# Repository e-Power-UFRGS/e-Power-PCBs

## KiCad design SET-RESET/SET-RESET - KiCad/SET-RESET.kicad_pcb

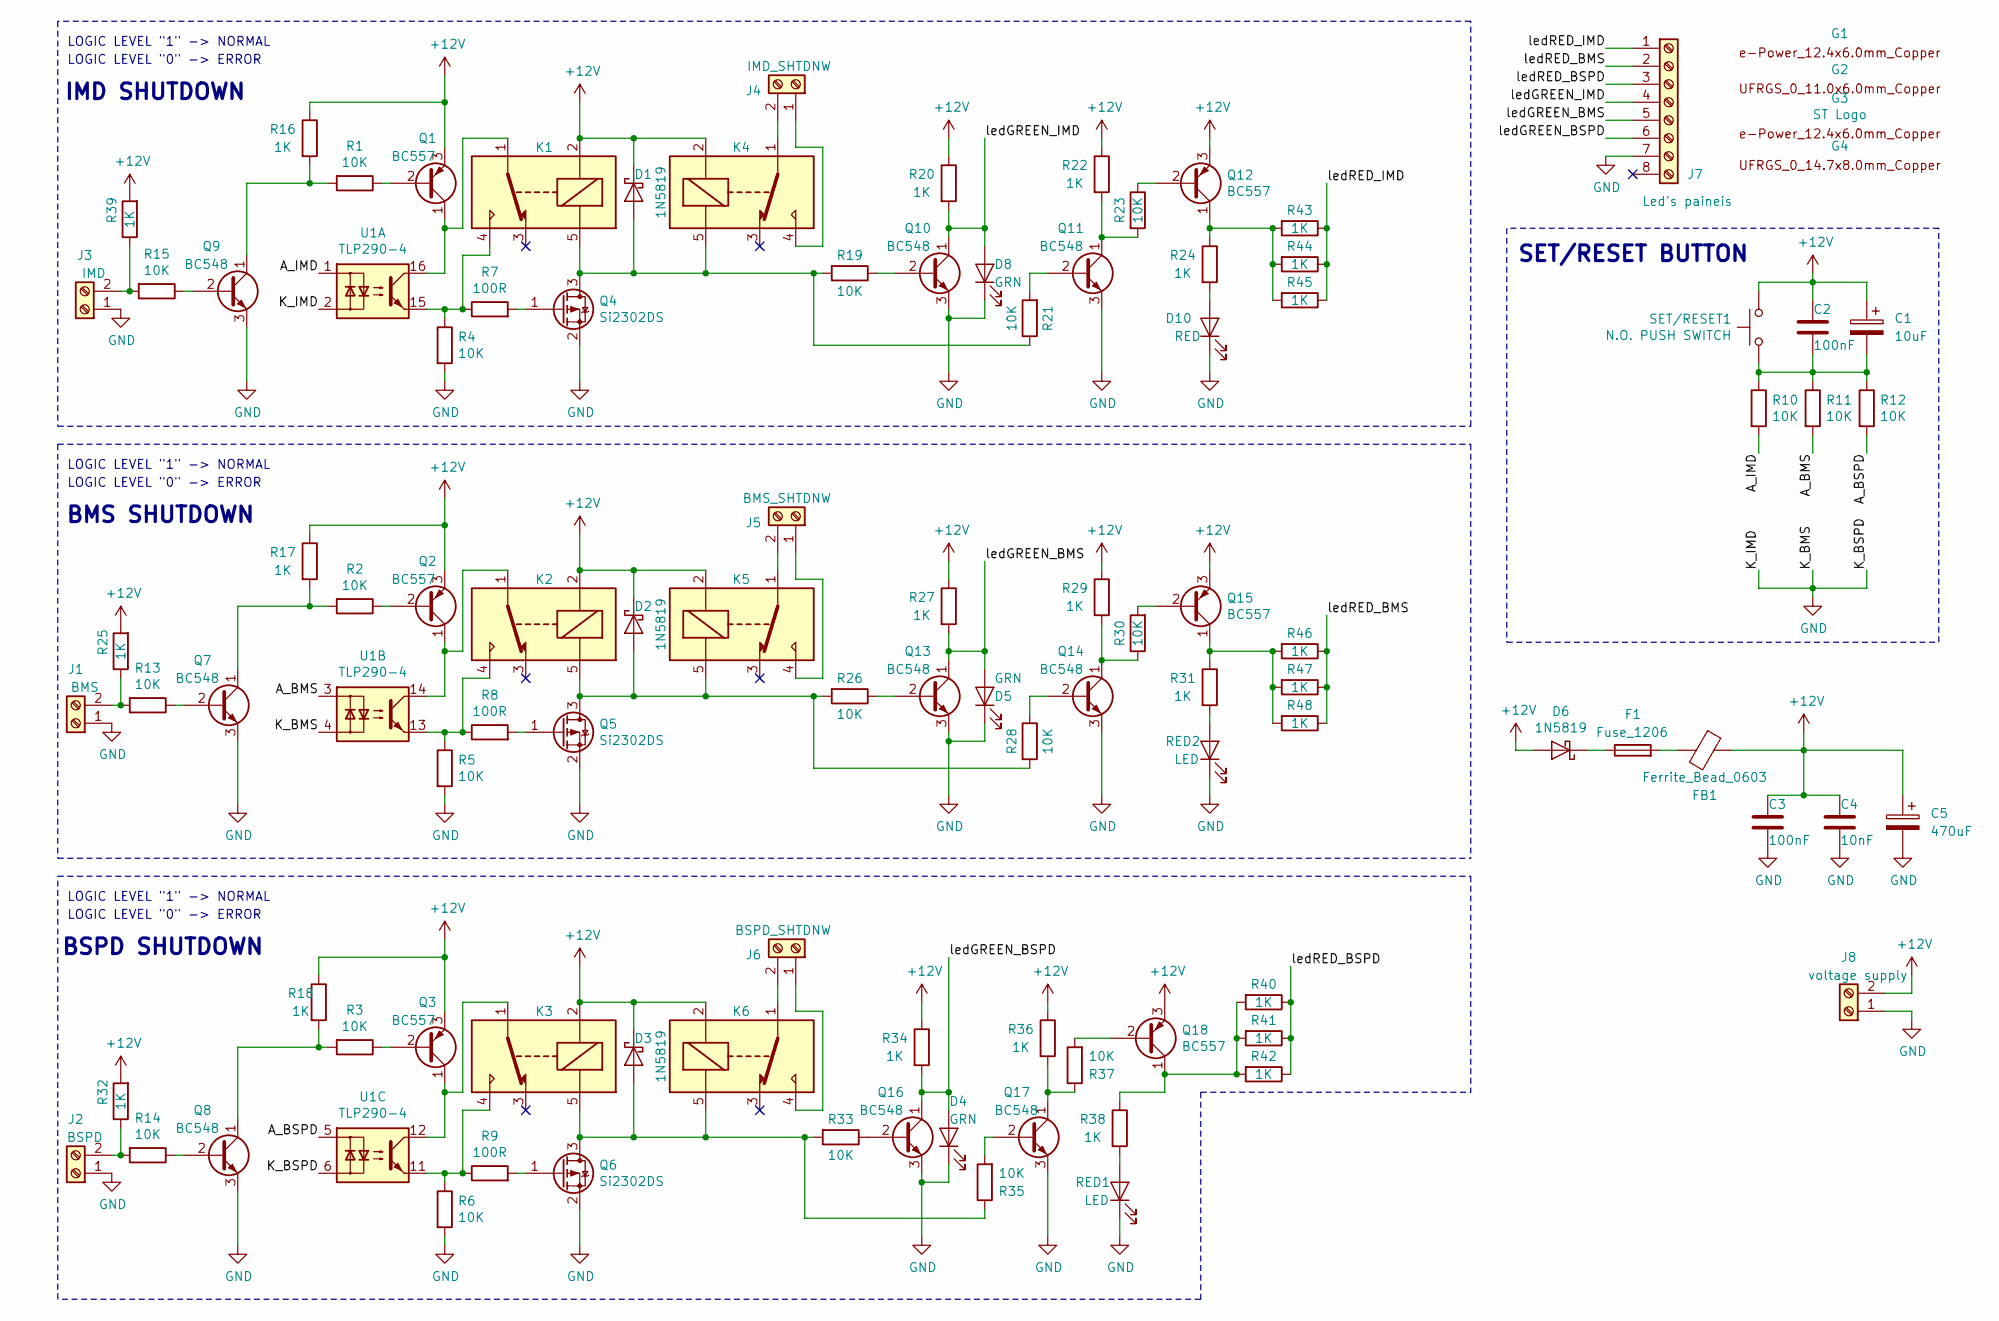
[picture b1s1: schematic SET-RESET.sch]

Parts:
C1: 10uF; CP_Elec_4x5.3
C2, C3: 100nF; C_0603_1608Metric_Pad1.05x0.95mm_HandSolder
C4: 10nF; C_0603_1608Metric_Pad1.05x0.95mm_HandSolder
C5: 470uF; CP_Elec_4x5.3
D1, D2, D3, D6: 1N5819; DO-41_SMD
D4, D5, D8: GRN; LED_0805_1.15x1.40mm_HandSolder
D10: RED; LED_0805_1.15x1.40mm_HandSolder
F1: Fuse_1206; FUSE_1206_3216Metric
FB1: Ferrite_Bead_0603; FB_0603_1608Metric
G1: e-Power_12.4x6.0mm_Copper; e-Power_16.5x8.0mm_Copper
G2: UFRGS_1_11.0x6.0mm_Copper; ESD-Logo_8.9x8mm_Copper
G3: ST Logo; ST_6.5x4.1mm_Copper
G4: UFRGS_1_14.7x8.0mm_Copper; UFRGS_14.7x8.0mm_Copper
J1: BMS; PhoenixContact_GMSTBA_2,5_2-G_1x02_P7.50mm_Horizontal
J2: BSPD; PhoenixContact_GMSTBA_2,5_2-G_1x02_P7.50mm_Horizontal
J3: IMD; PhoenixContact_GMSTBA_2,5_2-G_1x02_P7.50mm_Horizontal
J4: IMD_SHTDNW; PhoenixContact_GMSTBA_2,5_2-G_1x02_P7.50mm_Horizontal
J5: BMS_SHTDNW; PhoenixContact_GMSTBA_2,5_2-G_1x02_P7.50mm_Horizontal
J6: BSPD_SHTDNW; PhoenixContact_GMSTBA_2,5_2-G_1x02_P7.50mm_Horizontal
J7: Led's paineis; PinHeader_1x08_P1.27mm_Vertical
J8: voltage supply; PhoenixContact_GMSTBA_2,5_2-G_1x02_P7.50mm_Horizontal
K1, K2, K3, K4, K5, K6: RELAY_19.1x15.5mm; Relay_SPDT_SANYOU_SRD
Q1, Q2, Q3, Q12, Q15, Q18: BC557; SOT-23
Q4, Q5, Q6: Si2302DS; SOT-23
Q7, Q8, Q9, Q10, Q11, Q13, Q14, Q16, Q17: BC548; SOT-23
R1, R2, R3, R4, R5, R6, R10, R11, R12, R13, R14, R15, R19, R21, R23, R26, R28, R30, R33, R35, R37: 10K; R_1206_3216Metric
R7, R8, R9: 100R; R_1206_3216Metric
R16, R17, R18, R20, R22, R24, R25, R27, R29, R31, R32, R34, R36, R38, R39, R40, R41, R42, R43, R44, R45, R46, R47, R48: 1K; R_1206_3216Metric
RED1, RED2: LED; LED_0805_1.15x1.40mm_HandSolder
SET/RESET1: SW_Push; PhoenixContact_GMSTBA_2,5_2-G_1x02_P7.50mm_Horizontal
U1: TLP290-4

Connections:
+12V: C1.1, C2.1, C3.1, C4.1, C5.1, D1.1 (K), D2.1 (K), D3.1 (K), D6.2 (A), FB1.1, J8.2, K1.2, K2.2, K3.2, K4.2, K5.2, K6.2, Q1.3 (E), Q2.3 (E), Q3.3 (E), Q12.3 (E), Q15.3 (E), Q18.3 (E), R16.1, R17.1, R18.1, R20.1, R22.1, R25.2, R27.1, R29.1, R32.2, R34.1, R36.1, R39.2, SET/RESET1.1
/A_BMS: R11.2, U1.3
/A_BSPD: R12.2, U1.5
/A_IMD: R10.2, U1.1
/ledGREEN_BMS: D5.2 (A), J7.5, Q13.1 (C), R27.2
/ledGREEN_BSPD: D4.2 (A), J7.6, Q16.1 (C), R34.2
/ledGREEN_IMD: D8.2 (A), J7.4, Q10.1 (C), R20.2
/ledRED_BMS: J7.2, R46.1, R47.1, R48.1
/ledRED_BSPD: J7.3, R40.1, R41.1, R42.1
/ledRED_IMD: J7.1, R43.1, R44.1, R45.1
GND: C3.2, C4.2, C5.2, D4.1 (K), D5.1 (K), D8.1 (K), D10.1 (K), J1.1, J2.1, J3.1, J7.7, J8.1, Q4.2 (S), Q5.2 (S), Q6.2 (S), Q7.3 (E), Q8.3 (E), Q9.3 (E), Q10.3 (E), Q11.3 (E), Q13.3 (E), Q14.3 (E), Q16.3 (E), Q17.3 (E), R4.2, R5.2, R6.2, RED1.1 (K), RED2.1 (K), U1.2, U1.4, U1.6
unnamed: C1.2, C2.2, R10.1, R11.1, R12.1, SET/RESET1.2
unnamed: D1.2 (A), K1.5, K4.5, Q4.3 (D), R19.2, R21.1
unnamed: D2.2 (A), K2.5, K5.5, Q5.3 (D), R26.2, R28.2
unnamed: D3.2 (A), K3.5, K6.5, Q6.3 (D), R33.2, R35.1
unnamed: D6.1 (K), F1.1
unnamed: D10.2 (A), R24.2
unnamed: F1.2, FB1.2
unnamed: J1.2, R13.2, R25.1
unnamed: J2.2, R14.2, R32.1
unnamed: J3.2, R15.2, R39.1
unnamed: J4.1, K4.4
unnamed: J4.2, K4.1
unnamed: J5.1, K5.4
unnamed: J5.2, K5.1
unnamed: J6.1, K6.4
unnamed: J6.2, K6.1
unnamed: K1.1, Q1.1 (C), U1.16
unnamed: K1.4, R4.1, R7.1, U1.15
unnamed: K2.1, Q2.1 (C), U1.14
unnamed: K2.4, R5.1, R8.1, U1.13
unnamed: K3.1, Q3.1 (C), U1.12
unnamed: K3.4, R6.1, R9.1, U1.11
unnamed: Q1.2 (B), R1.1
unnamed: Q2.2 (B), R2.1
unnamed: Q3.2 (B), R3.1
unnamed: Q4.1 (G), R7.2
unnamed: Q5.1 (G), R8.2
unnamed: Q6.1 (G), R9.2
unnamed: Q7.1 (C), R2.2, R17.2
unnamed: Q7.2 (B), R13.1
unnamed: Q8.1 (C), R3.2, R18.2
unnamed: Q8.2 (B), R14.1
unnamed: Q9.1 (C), R1.2, R16.2
unnamed: Q9.2 (B), R15.1
unnamed: Q10.2 (B), R19.1
unnamed: Q11.1 (C), R22.2, R23.2
unnamed: Q11.2 (B), R21.2
unnamed: Q12.1 (C), R24.1, R43.2, R44.2, R45.2
unnamed: Q12.2 (B), R23.1
unnamed: Q13.2 (B), R26.1
unnamed: Q14.1 (C), R29.2, R30.1
unnamed: Q14.2 (B), R28.1
unnamed: Q15.1 (C), R31.1, R46.2, R47.2, R48.2
unnamed: Q15.2 (B), R30.2
unnamed: Q16.2 (B), R33.1
unnamed: Q17.1 (C), R36.2, R37.1
unnamed: Q17.2 (B), R35.2
unnamed: Q18.1 (C), R38.1, R40.2, R41.2, R42.2
unnamed: Q18.2 (B), R37.2
unnamed: R31.2, RED2.2 (A)
unnamed: R38.2, RED1.2 (A)

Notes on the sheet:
LOGIC LEVEL "1" -> NORMAL
LOGIC LEVEL "0" -> ERROR
BMS SHUTDOWN
SET/RESET BUTTON
IMD SHUTDOWN
BSPD SHUTDOWN

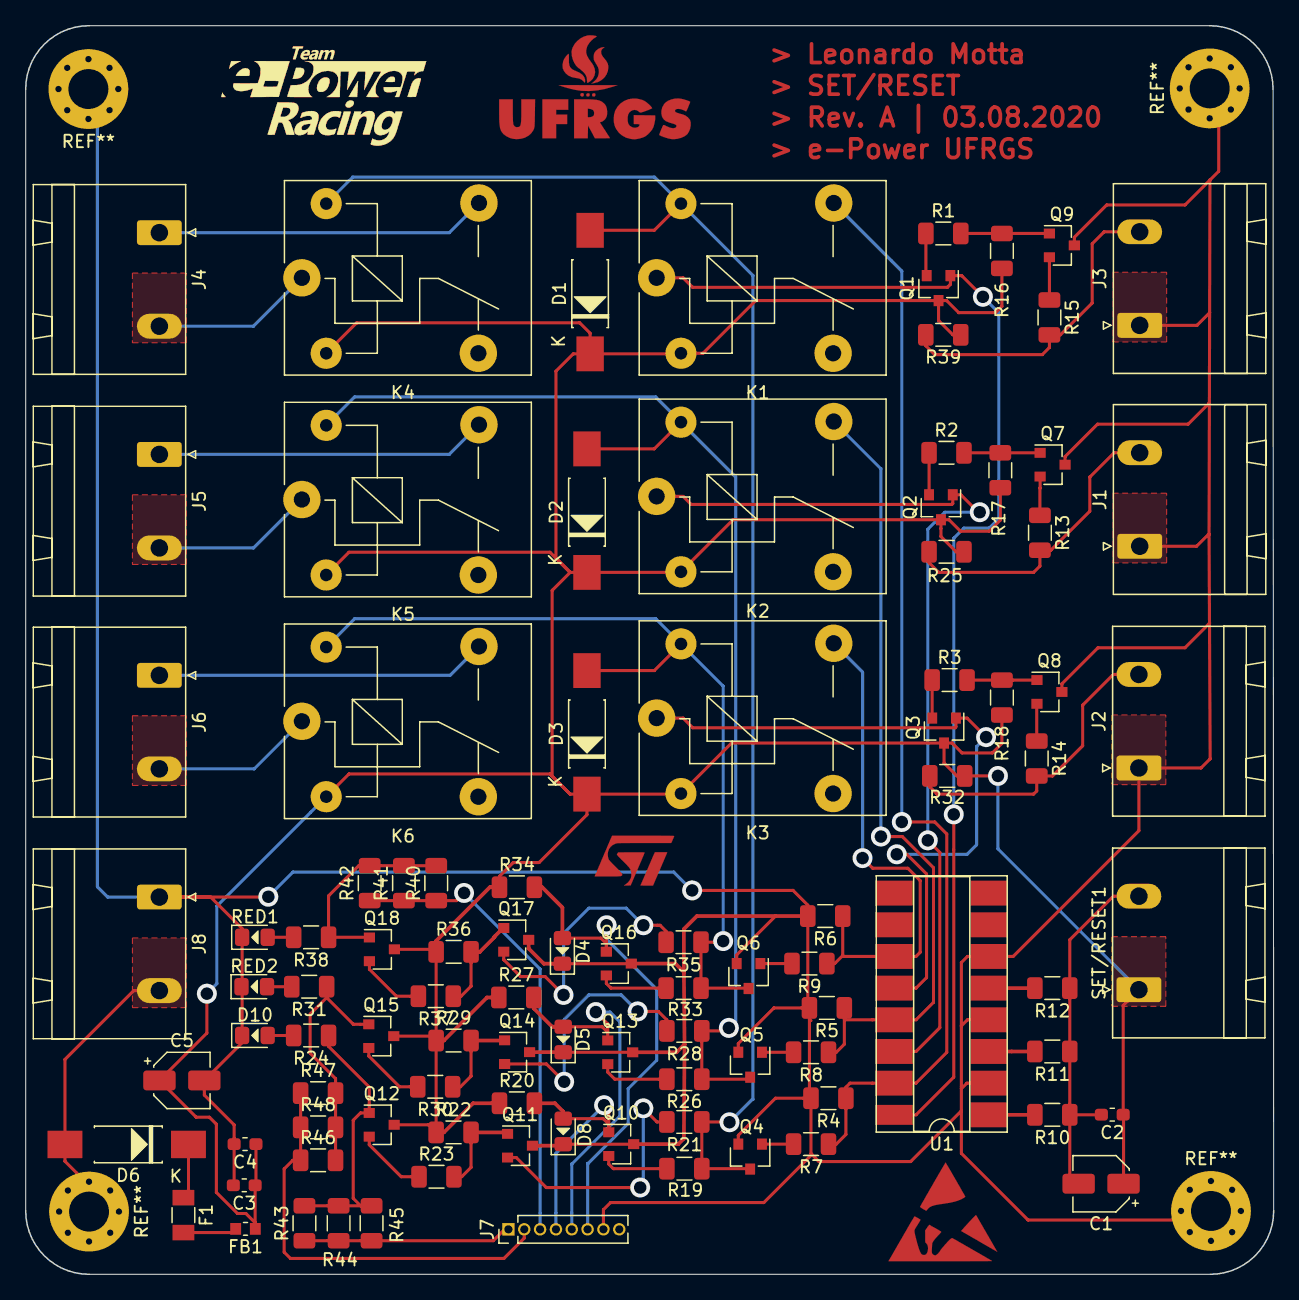
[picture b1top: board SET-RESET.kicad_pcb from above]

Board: 2 copper layers, 100.1 x 100.1 mm, 103 parts (0 on the bottom side), 62 nets.

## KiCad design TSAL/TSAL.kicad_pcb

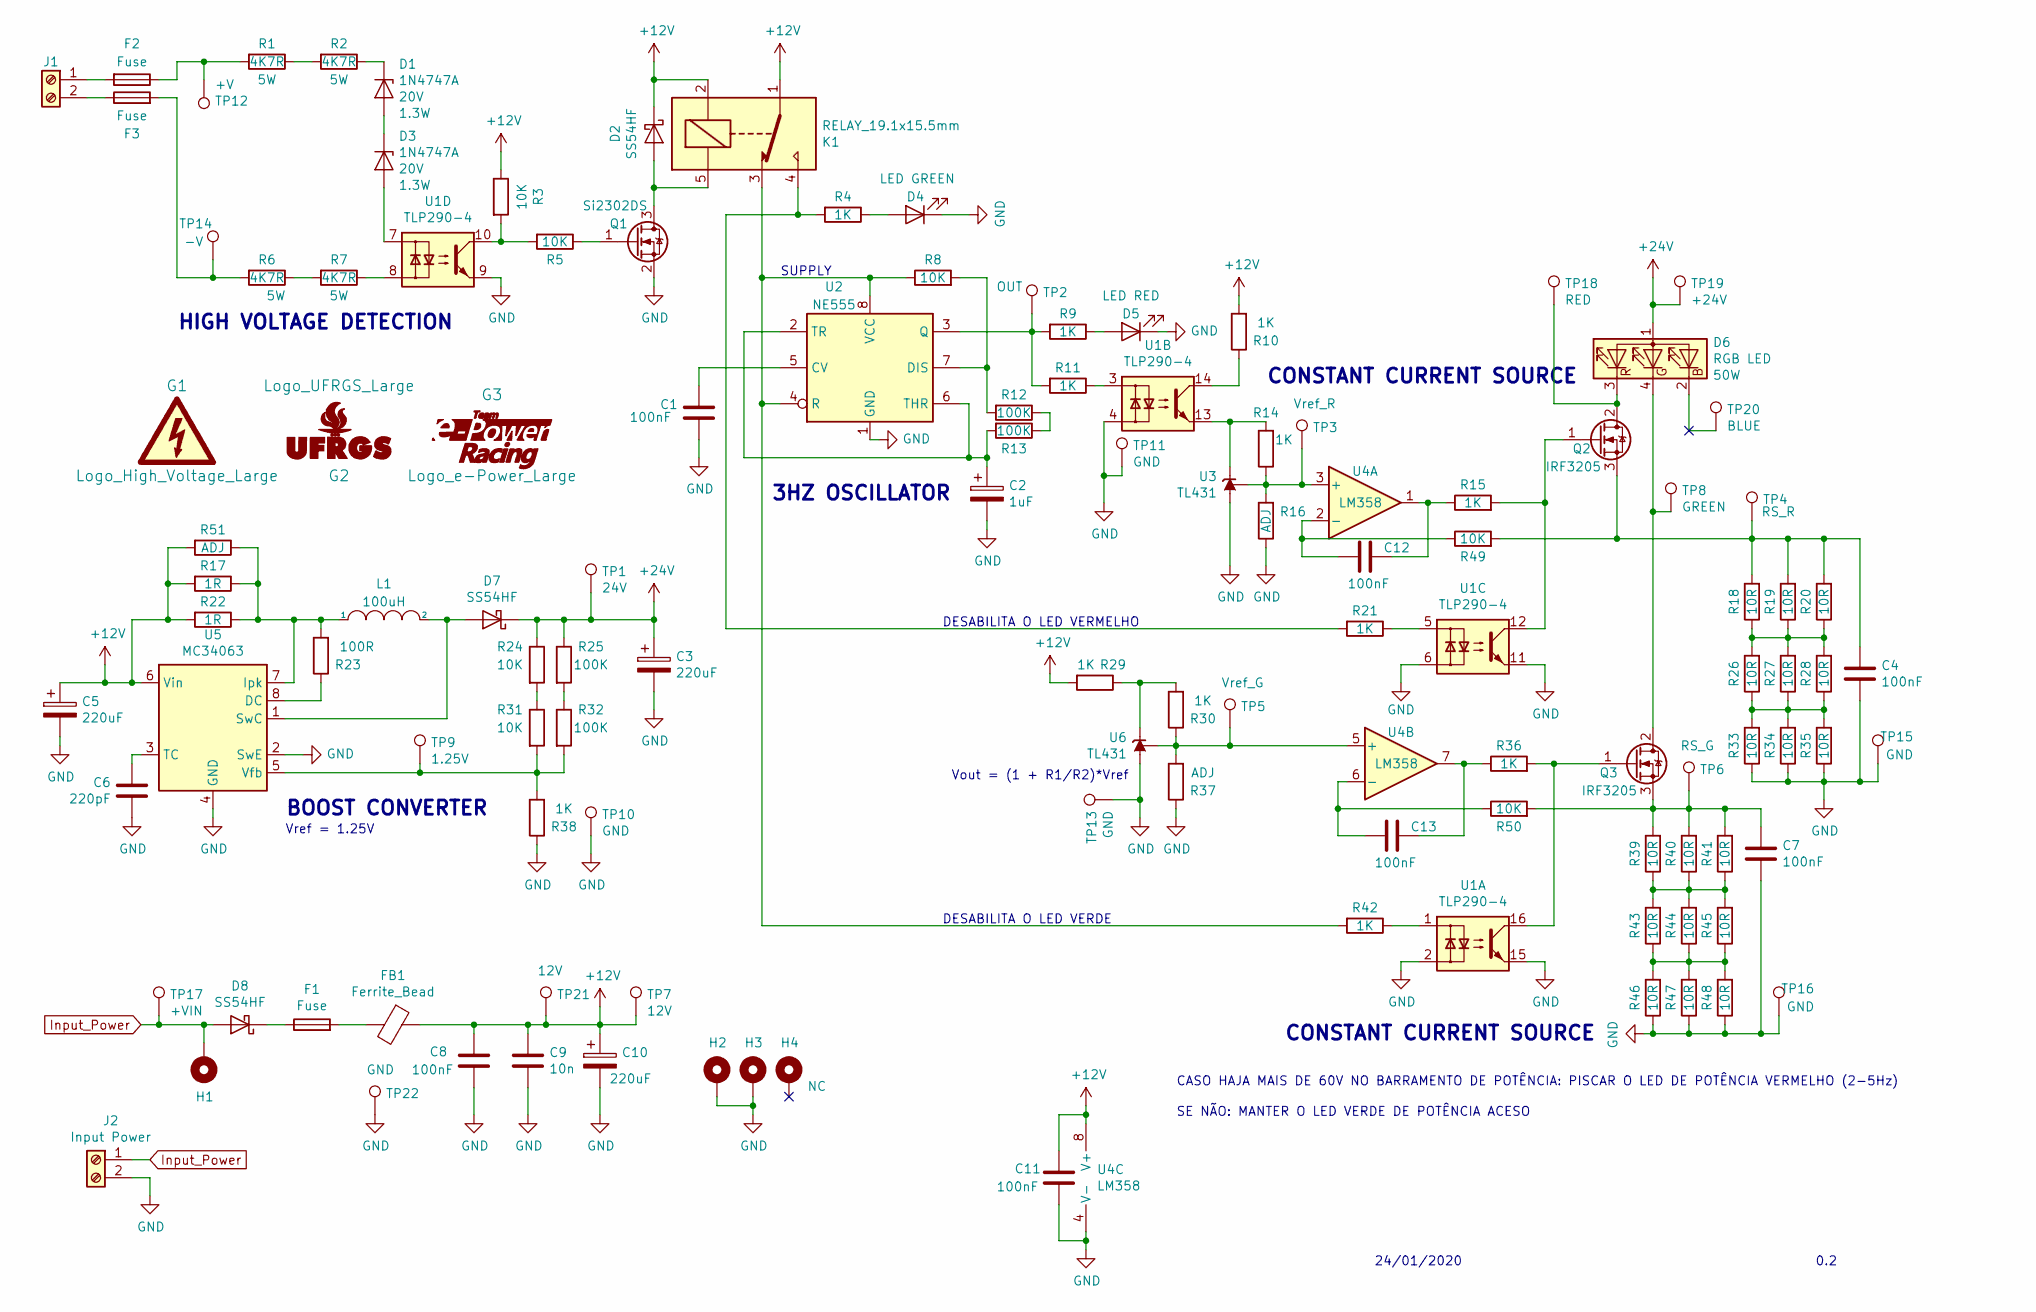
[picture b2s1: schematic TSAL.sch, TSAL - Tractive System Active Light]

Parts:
C1, C4, C7, C8, C11, C12, C13: 100nF; C_0805_2012Metric; Voltage 50V; LCSC C49678
C2: 1uF; C_0805_2012Metric; Voltage 50V; LCSC C28323
C3, C5, C10: 220uF; CP_Elec_10x10; LCSC C311611
C6: 220pF; C_0805_2012Metric; Voltage 50V; LCSC C53172
C9: 10n; C_0805_2012Metric; LCSC C1710
D1, D3: 1N4747A; DO-35_SMD; Voltage 20V
D2, D7, D8: SS54HF; DO-214AC; LCSC C22452
D4: LED GREEN; LED_0603_1608Metric; LCSC C72043
D5: LED RED; LED_0603_1608Metric; LCSC C2286
D6: RGB LED; TerminalBlock_Phoenix_MKDS-1,5-4-5.08_1x04_P5.08mm_Horizont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
F1, F2, F3: Fuse; FUSE_1206_3216Metric; LCSC C182445
FB1: Ferrite_Bead; FB_0603_1608Metric; LCSC C1002
G1: Logo_High_Voltage_Large; Logo_High_Voltage_13.7x12.0mm_SilkS
G2: Logo_UFRGS_Large; Logo_UFRGS_14.7x8.0mm_SilkS
G3: Logo_e-Power_Large; Logo_e-Power_22.8x12.0mm_SilkS
H1: +VIN; MountingHole_3.2mm_M3_Pad_Via
H2, H3: GND; MountingHole_3.2mm_M3_Pad_Via
H4: NC; MountingHole_3.2mm_M3_Pad_Via
J1: Tractive System; TerminalBlock_Phoenix_MKDS-1,5-2_1x02_P5.08mm_Horizontal
J2: Input Power; TerminalBlock_Phoenix_MKDS-1,5-2_1x02_P5.08mm_Horizontal
K1: RELAY_19.1x15.5mm; Relay_SPDT_SANYOU_SRD
L1: 100uH; L_12x12mm_H6mm; LCSC C169389
Q1: Si2302DS; SOT-23
Q2, Q3: IRF3205; TO-220-3_Horizontal_TabDown
R1, R2, R6, R7: 4K7R; R_Axial_DIN0617_L17.0mm_D6.0mm_P25.40mm_Horizontal
R3, R5, R8: 10K; R_0805_2012Metric; LCSC C17414
R4, R9, R10, R11, R14, R15, R21, R29, R30, R36, R38, R42: 1K; R_0805_2012Metric; LCSC C17513
R12, R13: 100K; R_0805_2012Metric; LCSC C17407
R16, R37: ADJ; R_0805_2012Metric
R17, R22: 1R; R_0805_2012Metric; LCSC C25271
R18, R19, R20, R26, R27, R28, R33, R34, R35, R39, R40, R41, R43, R44, R45, R46, R47, R48: 10R; R_0805_2012Metric; LCSC C17415
R23: 100R; R_0805_2012Metric; LCSC C17408
R24, R31, R49, R50: 10K; R_0805_2012Metric; LCSC C17513
R25, R32: 100K; R_0805_2012Metric; LCSC C17513
R51: ADJ; R_0805_2012Metric; LCSC C25271
TP1: 24V; TestPoint_Pad_D1.0mm
TP2: OUT; TestPoint_Pad_D1.0mm
TP3: Vref_R; TestPoint_Pad_D1.0mm
TP4: RS_R; TestPoint_Pad_D1.0mm
TP5: Vref_G; TestPoint_Pad_D1.0mm
TP6: RS_G; TestPoint_Pad_D1.0mm
TP7, TP21: 12V; TestPoint_Pad_D1.0mm
TP8: GREEN; TestPoint_Pad_D1.0mm
TP9: 1.25V; TestPoint_Pad_D1.0mm
TP10, TP11, TP13, TP15, TP16, TP22: GND; TestPoint_Pad_D1.0mm
TP12: +V; TestPoint_Pad_D1.0mm
TP14: -V; TestPoint_Pad_D1.0mm
TP17: +VIN; TestPoint_Pad_D1.0mm
TP18: RED; TestPoint_Pad_D1.0mm
TP19: +24V; TestPoint_Pad_D1.0mm
TP20: BLUE; TestPoint_Pad_D1.0mm
U1: TLP290-4; SOIC-16_4.55x10.3mm_P1.27mm(TLP290-4); LCSC C39031
U2: NE555; SOIC-8_3.9x4.9mm_P1.27mm; LCSC C7593
U3, U6: TL431; SOT-23
U4: LM358; SOIC-8_3.9x4.9mm_P1.27mm; LCSC C7950
U5: MC34063; SOIC-8_3.9x4.9mm_P1.27mm; LCSC C32078

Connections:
+12V: C5.1, C8.1, C9.1, C10.1, C11.1, D2.1 (K), FB1.1, K1.1, K1.2, R3.1, R10.2, R17.2, R22.2, R29.2, R51.2, TP7.1, TP21.1, U4.8 (V+), U5.6 (Vin)
+24V: C3.1, D6.1 (A), D7.1 (K), R24.1, R25.1, TP1.1, TP19.1
GND: C1.1, C2.2, C3.2, C4.1, C5.2, C6.1, C7.1, C8.2, C9.2, C10.2, C11.2, D4.1 (K), D5.1 (K), H2.1, H3.1, J2.2, Q1.2 (S), R16.1, R33.1, R34.1, R35.1, R37.1, R38.1, R46.1, R47.1, R48.1, TP10.1, TP11.1, TP13.1, TP15.1, TP16.1, TP22.1, U1.2, U1.4, U1.6, U1.9, U1.11, U1.15, U2.1 (GND), U3.3 (A), U4.4 (V-), U5.2 (SwE), U5.4 (GND), U6.3 (A)
Input_Power: D8.2 (A), H1.1, J2.1, TP17.1
unnamed: C1.2, U2.5 (CV)
unnamed: C2.1, R13.2, U2.2 (TR), U2.6 (THR)
unnamed: C4.2, Q2.3 (S), R18.2, R19.2, R20.2, R49.2, TP4.1
unnamed: C6.2, U5.3 (TC)
unnamed: C7.2, Q3.3 (S), R39.2, R40.2, R41.2, R50.2, TP6.1
unnamed: C12.1, R49.1, U4.2 (-)
unnamed: C12.2, R15.1, U4.1
unnamed: C13.1, R50.1, U4.6 (-)
unnamed: C13.2, R36.1, U4.7
unnamed: D1.1 (K), R2.1
unnamed: D1.2 (A), D3.1 (K)
unnamed: D2.2 (A), K1.5, Q1.3 (D)
unnamed: D3.2 (A), U1.7
unnamed: D4.2 (A), R4.1
unnamed: D5.2 (A), R9.1
unnamed: D6.2 (BK), TP20.1
unnamed: D6.3 (RK), Q2.2 (D), TP18.1
unnamed: D6.4 (GK), Q3.2 (D), TP8.1
unnamed: D7.2 (A), L1.2, U5.1 (SwC)
unnamed: D8.1 (K), F1.1
unnamed: F1.2, FB1.2
unnamed: F2.1, R1.2, TP12.1
unnamed: F2.2, J1.1
unnamed: F3.1, J1.2
unnamed: F3.2, R6.2, TP14.1
unnamed: K1.3, R8.1, R42.2, U2.4 (R), U2.8 (VCC)
unnamed: K1.4, R4.2, R21.2
unnamed: L1.1, R17.1, R22.1, R23.2, R51.1, U5.7 (Ipk)
unnamed: Q1.1 (G), R5.1
unnamed: Q2.1 (G), R15.2, U1.12
unnamed: Q3.1 (G), R36.2, U1.16
unnamed: R1.1, R2.2
unnamed: R3.2, R5.2, U1.10
unnamed: R6.1, R7.2
unnamed: R7.1, U1.8
unnamed: R10.1, U1.14
unnamed: R11.1, U1.3
unnamed: R9.2, R11.2, TP2.1, U2.3 (Q)
unnamed: R12.1, R13.1
unnamed: R8.2, R12.2, U2.7 (DIS)
unnamed: R14.1, R16.2, TP3.1, U3.1 (REF), U4.3 (+)
unnamed: R14.2, U1.13, U3.2 (K)
unnamed: R18.1, R19.1, R20.1, R26.2, R27.2, R28.2
unnamed: R21.1, U1.5
unnamed: R23.1, U5.8 (DC)
unnamed: R24.2, R31.1
unnamed: R25.2, R32.1
unnamed: R26.1, R27.1, R28.1, R33.2, R34.2, R35.2
unnamed: R29.1, R30.2, U6.2 (K)
unnamed: R30.1, R37.2, TP5.1, U4.5 (+), U6.1 (REF)
unnamed: R31.2, R32.2, R38.2, TP9.1, U5.5 (Vfb)
unnamed: R39.1, R40.1, R41.1, R43.2, R44.2, R45.2
unnamed: R42.1, U1.1
unnamed: R43.1, R44.1, R45.1, R46.2, R47.2, R48.2

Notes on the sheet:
HIGH VOLTAGE DETECTION
24/01/2020
0.2
CASO HAJA MAIS DE 60V NO BARRAMENTO DE POTÊNCIA: PISCAR O LED DE POTÊNCIA VERMELHO (2-5Hz)
SE NÃO: MANTER O LED VERDE DE POTÊNCIA ACESO
BOOST CONVERTER
3HZ OSCILLATOR
DESABILITA O LED VERMELHO
DESABILITA O LED VERDE
CONSTANT CURRENT SOURCE
SUPPLY
Vout = (1 + R1/R2)*Vref
Vref = 1.25V

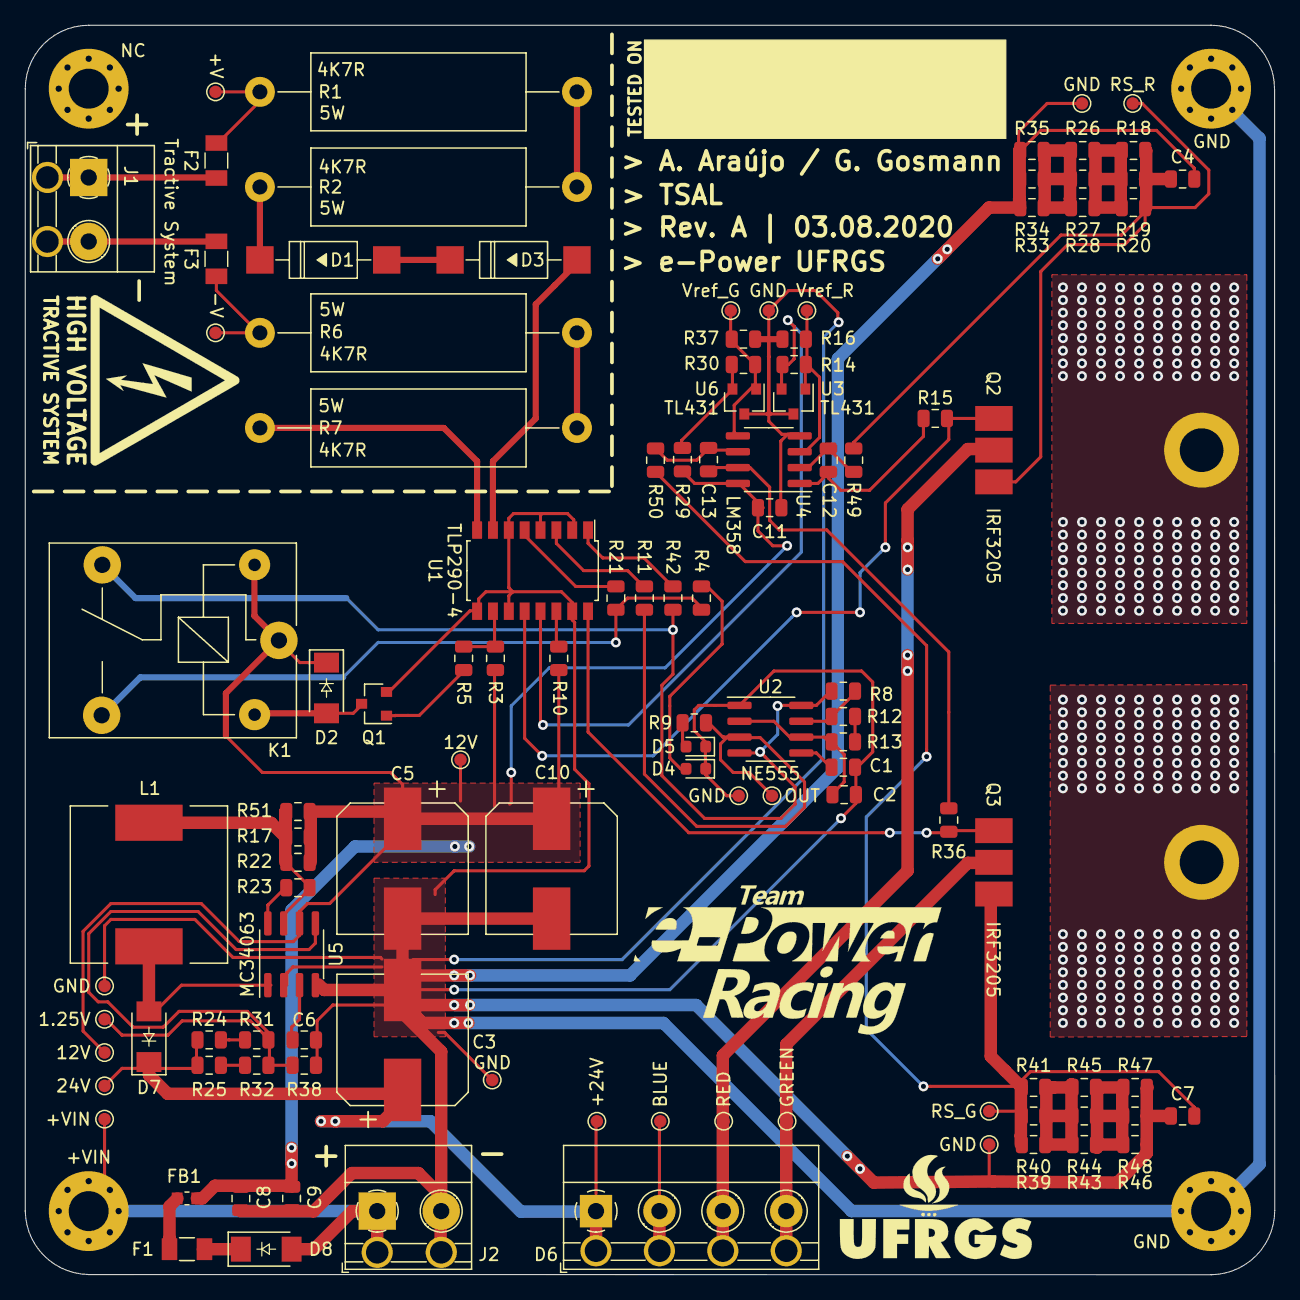
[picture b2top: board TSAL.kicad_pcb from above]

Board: 2 copper layers, 100.1 x 100.1 mm, 118 parts (0 on the bottom side), 58 nets.

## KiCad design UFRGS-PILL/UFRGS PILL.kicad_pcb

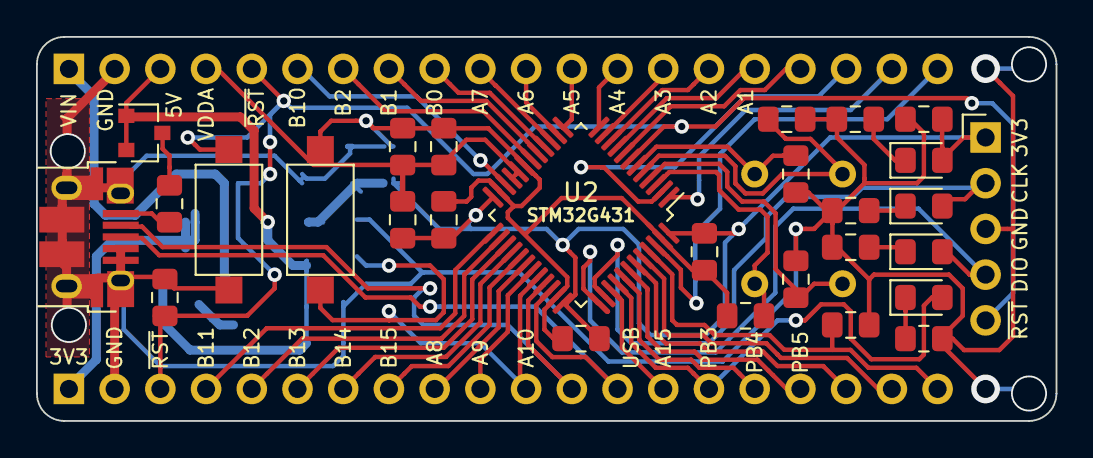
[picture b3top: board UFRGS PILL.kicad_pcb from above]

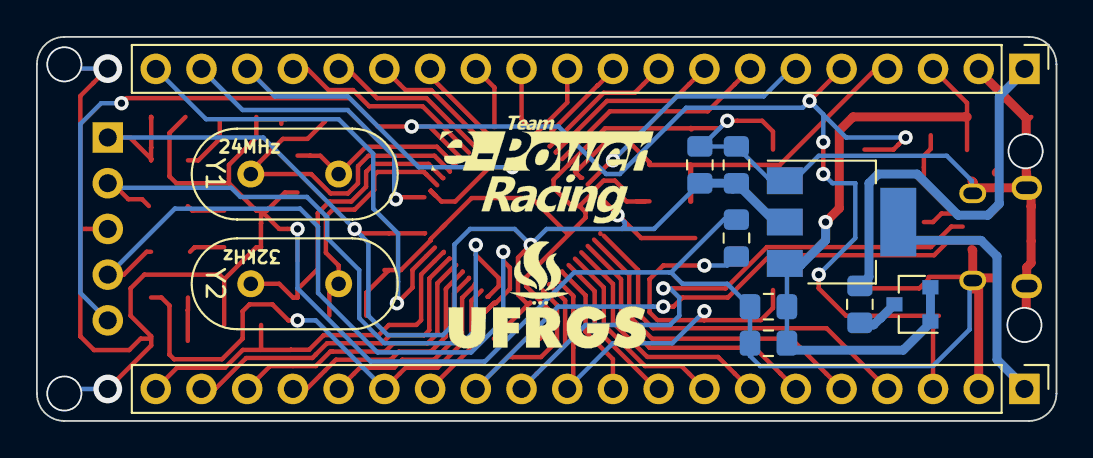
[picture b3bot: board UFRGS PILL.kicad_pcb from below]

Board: 2 copper layers, 56.6 x 21.3 mm, 40 parts (12 on the bottom side), 51 nets.

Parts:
C1, C2, C5, C7, C11, C12, C13, C14, C15: 100nF; C_0805_2012Metric_Pad1.15x1.40mm_HandSolder
C3, C4: 12pF; C_0805_2012Metric_Pad1.15x1.40mm_HandSolder
C6, C8, C16: 10uF; C_0805_2012Metric_Pad1.15x1.40mm_HandSolder
C9, C10: 100pF; C_0805_2012Metric_Pad1.15x1.40mm_HandSolder
D1, D2: BAT54A; SOT-23
D3, D4, D5: GRN_LED; LED_0805_2012Metric_Pad1.15x1.40mm_HandSolder
D6: RED_LED; LED_0805_2012Metric_Pad1.15x1.40mm_HandSolder
FB1: Ferrite_Bead; R_0805_2012Metric_Pad1.15x1.40mm_HandSolder
J1: ST-LINK; PinHeader_1x05_P2.54mm_Horizontal
J2, J3: CONN_01x20; PinHeader_1x20_P2.54mm_Vertical
J4: USB_B_Micro; USB_Micro-B_Horizontal
R1, R3: 0R; R_0805_2012Metric_Pad1.15x1.40mm_HandSolder
R2: 10K; R_0805_2012Metric_Pad1.15x1.40mm_HandSolder
R4, R5, R6, R7: 330R; R_0805_2012Metric_Pad1.15x1.40mm_HandSolder
SW1, SW2: SW_Push; SW_SPST_CK_8.0x2.5x3.65mm
U1: AZ1117-3.3; SOT-223-3_TabPin2
U2: STM32G431CBTx; LQFP-48_7x7mm_P0.5mm
Y1: 24MHz; Crystal_HC49-4H_Vertical
Y2: 32K768Hz; Crystal_HC49-4H_Vertical

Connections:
+3V3: C7.1, C8.1, C11.1, C12.1, C13.1, C14.1, D6.2, FB1.2, J1.1, J2.1, U1.2, U2.24, U2.36, U2.48
+5V: C5.1, C6.1, D1.1, D1.2, D2.1, D2.2, J3.3, U1.3
GND: C1.2, C2.2, C3.2, C4.2, C5.2, C6.2, C7.2, C8.2, C9.2, C10.2, C11.2, C12.2, C13.2, C14.2, C15.2, C16.2, J1.3, J2.2, J3.2, J4.4, J4.5, J4.6, R2.2, R4.2, R5.2, R6.2, R7.2, SW1.2, SW2.2, U1.1, U2.19, U2.23, U2.35, U2.47
NRST: C2.1, J1.5, J2.3, J3.5, SW2.1, U2.7
unnamed: C3.1, U2.5, Y1.2
unnamed: C4.1, U2.6, Y1.1
unnamed: C9.1, U2.4, Y2.2
unnamed: C10.1, U2.3, Y2.1
unnamed: D1.3, R1.1
unnamed: D2.3, R3.1
unnamed: D3.1, R4.1
unnamed: D4.1, R5.1
unnamed: D5.1, R6.1
unnamed: D6.1, R7.1
unnamed: J4.1, R3.2
PA0: J3.17, U2.8
PA1: J3.16, U2.9
PA2: J3.15, U2.10
PA3: J3.14, U2.11
PA4: J3.13, U2.12
PA5: J3.12, U2.13
PA6: J3.11, U2.14
PA7: J3.10, U2.15
PA8: J2.9, U2.30
PA9: J2.10, U2.31
PA10: C1.1, J2.11, SW1.1, U2.32
PA15: J2.14, U2.39
PB0: J3.9, U2.16
PB1: J3.8, U2.17
PB2: J3.7, U2.18
PB3: D5.2, J2.15, U2.40
PB4: J2.16, U2.41
PB5: J2.17, U2.42
PB6: J2.18, U2.43
PB7: J2.19, U2.44
PB8: J2.20, R2.1, U2.45
PB9: J3.20, U2.46
PB10: J3.6, U2.22
PB11: J2.4, U2.25
PB12: J2.5, U2.26
PB13: J2.6, U2.27
PB14: J2.7, U2.28
PB15: J2.8, U2.29
PC13: J3.18, U2.2
T_SWCLK: D4.2, J1.2, U2.38
T_SWDIO: D3.2, J1.4, U2.37
USB_DM: J2.12, J4.2, U2.33
USB_DP: J2.13, J4.3, U2.34
VBAT: J3.19, U2.1
VDDA: C15.1, C16.1, FB1.1, J3.4, U2.20, U2.21
VIN: J3.1, R1.2
